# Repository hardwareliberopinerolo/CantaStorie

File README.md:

# Canta Storie realizzato con Arduino Mini Pro a 3.3V

Il Canta Storie riproduce brani MP3 (come le storie per i bambini) al passagio di Tag RFID

Le storie, in formato MP3, sono salvate su una SD Card e riprodotte dal lettore MP3 DFPlayer

I Tag RFID possono essere riciclati per esempio usando i biglietti usati dei mezzi pubblici che utilizzano questa tecnoligia

Arduino Mini Pro a 3.3V si occupa di gestire la lettura dei Tag RFID ed eseguire i brani MP3

Nella cartella [Arduino Sketches](/00_Arduino_Sketches) sono presenti gli Sketches da caricare su Arduino

Il Canta Storie è in grado di associare in modo automatico i Tag RFID ai brani MP3 che si vogliono riprodurre attraverso l'uso di un Tag RFID Master

**Materiale necessario**
- Arduino Mini Pro a 3.3V
- MP3 DFPlayer
- SD Card con file MP3
- Lettore RFID RC522
- Tessere/Tag RFID

Nella cartella [PCB Kicad](/01_PCB_Kicad) sono presenti gli schemi elettrici per costruire il circuito e il PCB

**Altre Versioni**

[Versione con Arduino Nano e RC522](/10_Other_Versions/Arduino_Nano_RC522): E' una versione che permette di usare Arduino Nano, in modo simile al progetto [TonUINO](https://github.com/seisfeld/TonUINO)

[Versione con Arduino Nano e PN532](/10_Other_Versions)

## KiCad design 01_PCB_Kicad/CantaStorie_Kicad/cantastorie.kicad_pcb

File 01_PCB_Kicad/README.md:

# Schemi e PCB
La cartella contiene il progetto Kicad

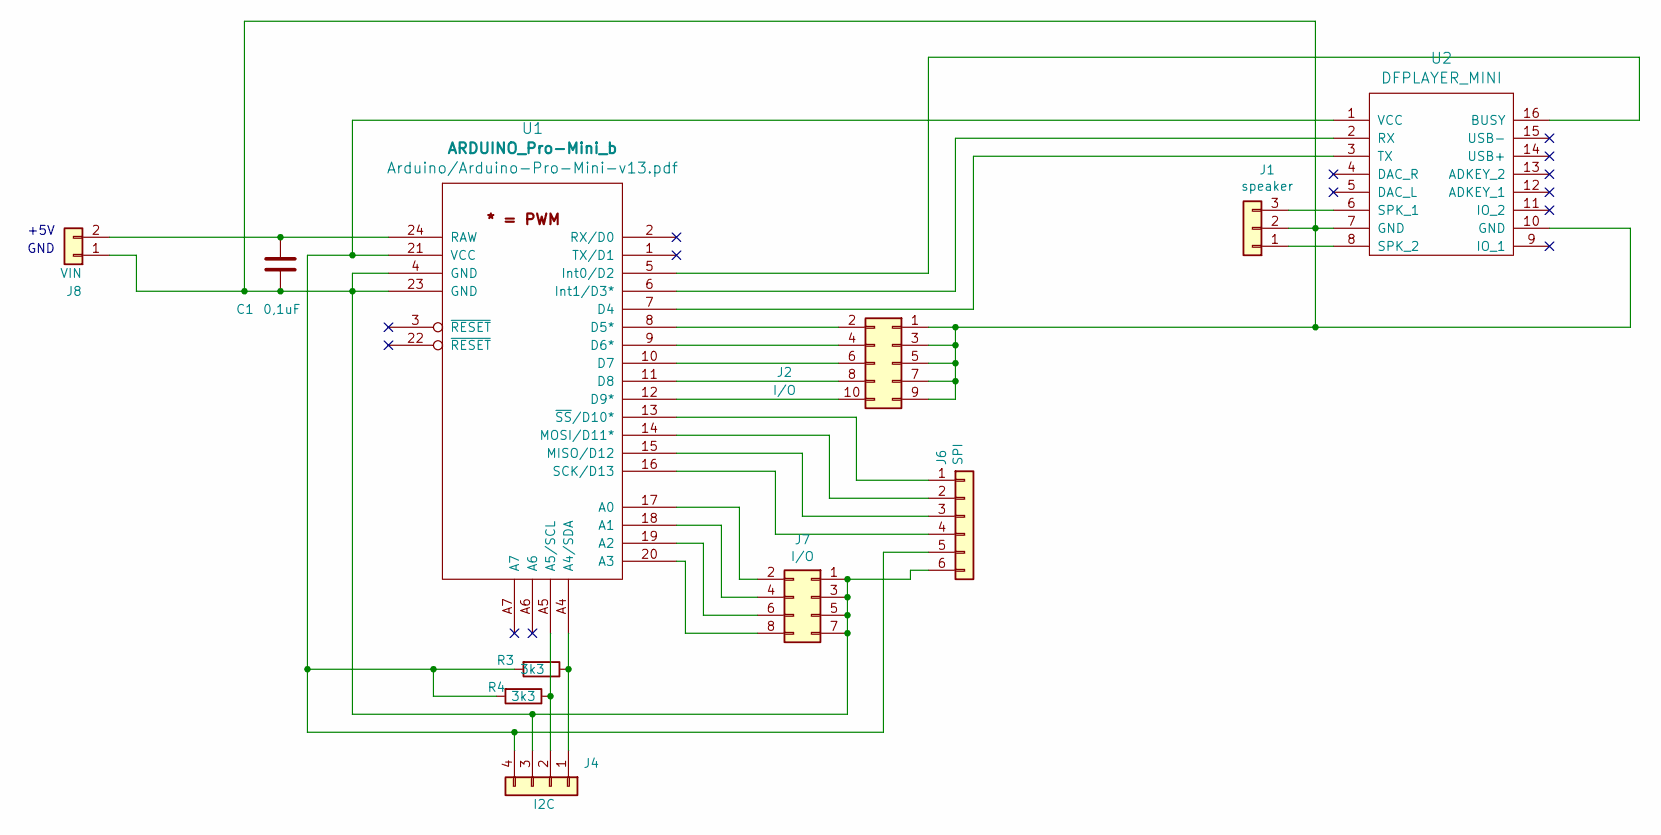
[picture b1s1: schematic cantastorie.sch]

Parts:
C1: 0,1uF; C_Disc_D6.0mm_W2.5mm_P5.00mm
J1: speaker; SL-103-X-XX_1x03
J2: I/O; SDL-110-X-XX_2x05
J4: I2C; SL-104-X-XX_1x04
J6: SPI; SL-106-X-XX_1x06
J7: I/O; SDL-108-X-XX_2x04
J8: VIN; SDL-102-X-XX_2x01
R3, R4: 3k3; R_Axial_DIN0204_L3.6mm_D1.6mm_P7.62mm_Horizontal
U1: ARDUINO_Pro-Mini_b; ARDUINO_Pro-MiniB_1
U2: DFPLAYER_MINI; DFPlayer_V3

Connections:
unnamed: C1.1, J8.2, U1.24 (RAW)
unnamed: C1.2, J1.2, J2.1, J2.3, J2.5, J2.7, J2.9, J4.3, J6.6, J7.1, J7.3, J7.5, J7.7, J8.1, U1.4 (GND), U1.23 (GND), U2.7 (GND), U2.10 (GND)
unnamed: J1.1, U2.8 (SPK_2)
unnamed: J1.3, U2.6 (SPK_1)
unnamed: J2.2, U1.8 (D5*)
unnamed: J2.4, U1.9 (D6*)
unnamed: J2.6, U1.10 (D7)
unnamed: J2.8, U1.11 (D8)
unnamed: J2.10, U1.12 (D9*)
unnamed: J4.1, R3.1, U1.A4 (A4/SDA)
unnamed: J4.2, R4.1, U1.A5 (A5/SCL)
unnamed: J4.4, J6.5, R3.2, R4.2, U1.21 (VCC), U2.1 (VCC)
unnamed: J6.1, U1.13 (~SS~/D10*)
unnamed: J6.2, U1.14 (MOSI/D11*)
unnamed: J6.3, U1.15 (MISO/D12)
unnamed: J6.4, U1.16 (SCK/D13)
unnamed: J7.2, U1.17 (A0)
unnamed: J7.4, U1.18 (A1)
unnamed: J7.6, U1.19 (A2)
unnamed: J7.8, U1.20 (A3)
unnamed: U1.5 (Int0/D2), U2.16 (BUSY)
unnamed: U1.6 (Int1/D3*), U2.2 (RX)
unnamed: U1.7 (D4), U2.3 (TX)

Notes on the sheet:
GND
+5V

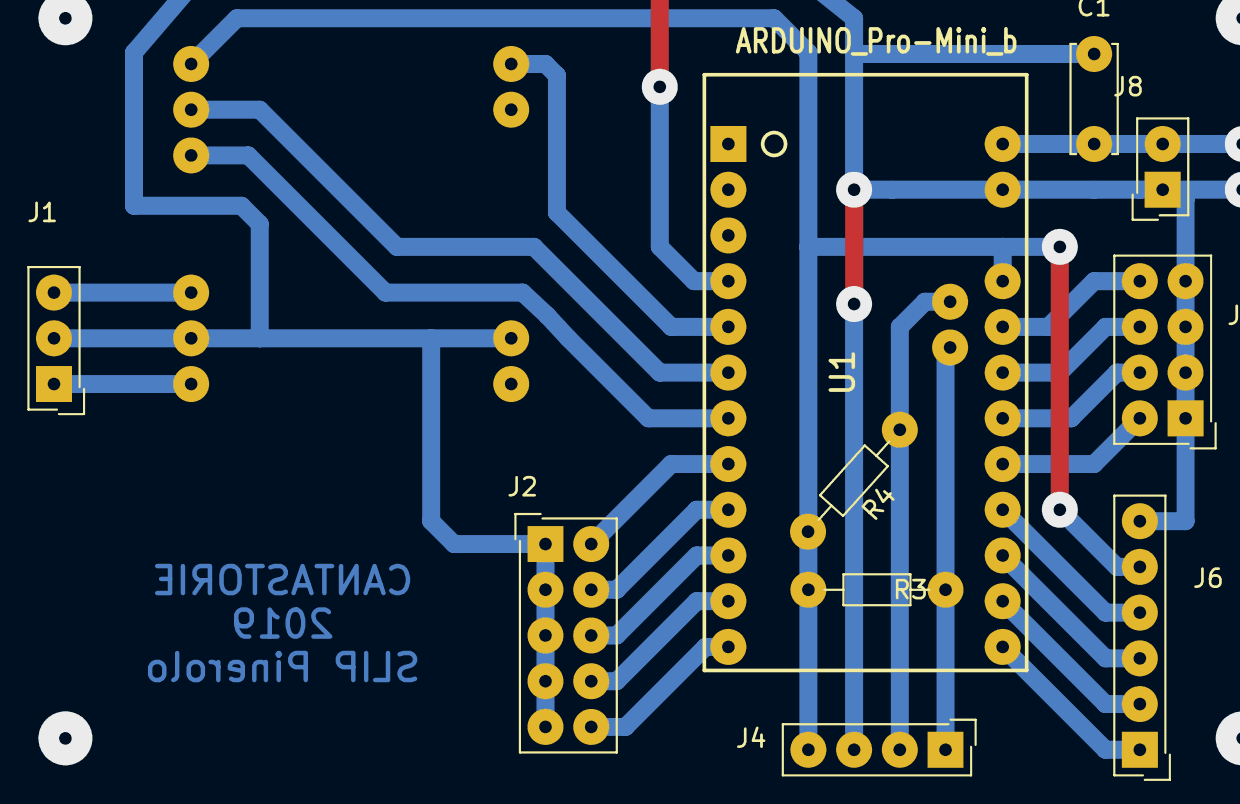
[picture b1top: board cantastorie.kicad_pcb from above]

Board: 2 copper layers, 11 parts (0 on the bottom side), 23 nets.

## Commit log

2019-08-05 Spostato progetto da RoboticBoyer
2019-08-10 new sketch rev 05
2019-08-10 new sketch rev 06
2019-08-24 219-08-24 Added Sketches for Tests
2019-12-23 Aggiornamento versione RC522
2020-08-27 Added version with Random Cards
2021-11-01 Canta Storie con Arduino Nano
